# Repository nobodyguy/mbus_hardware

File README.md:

# M-bus to USB board
* KiCAD 6.X required 
* includes ESD (USB+MBUS) and TVS (MBUS) protections
* includes AP3015 stepup from 5V -> 34V
* includes CH340E UART IC

## Software
Tested with https://github.com/ganehag/pyMeterBus library.

## 5V vs 3.3V note 
CH340E is 5V only IC without additional 3.3V regulator. Even its RX/TX pins are 5V.
Use PL2303GL instead when CH340E is not available and change MBUS logic to 3.3V (replace R6 and R10).

## Board overview

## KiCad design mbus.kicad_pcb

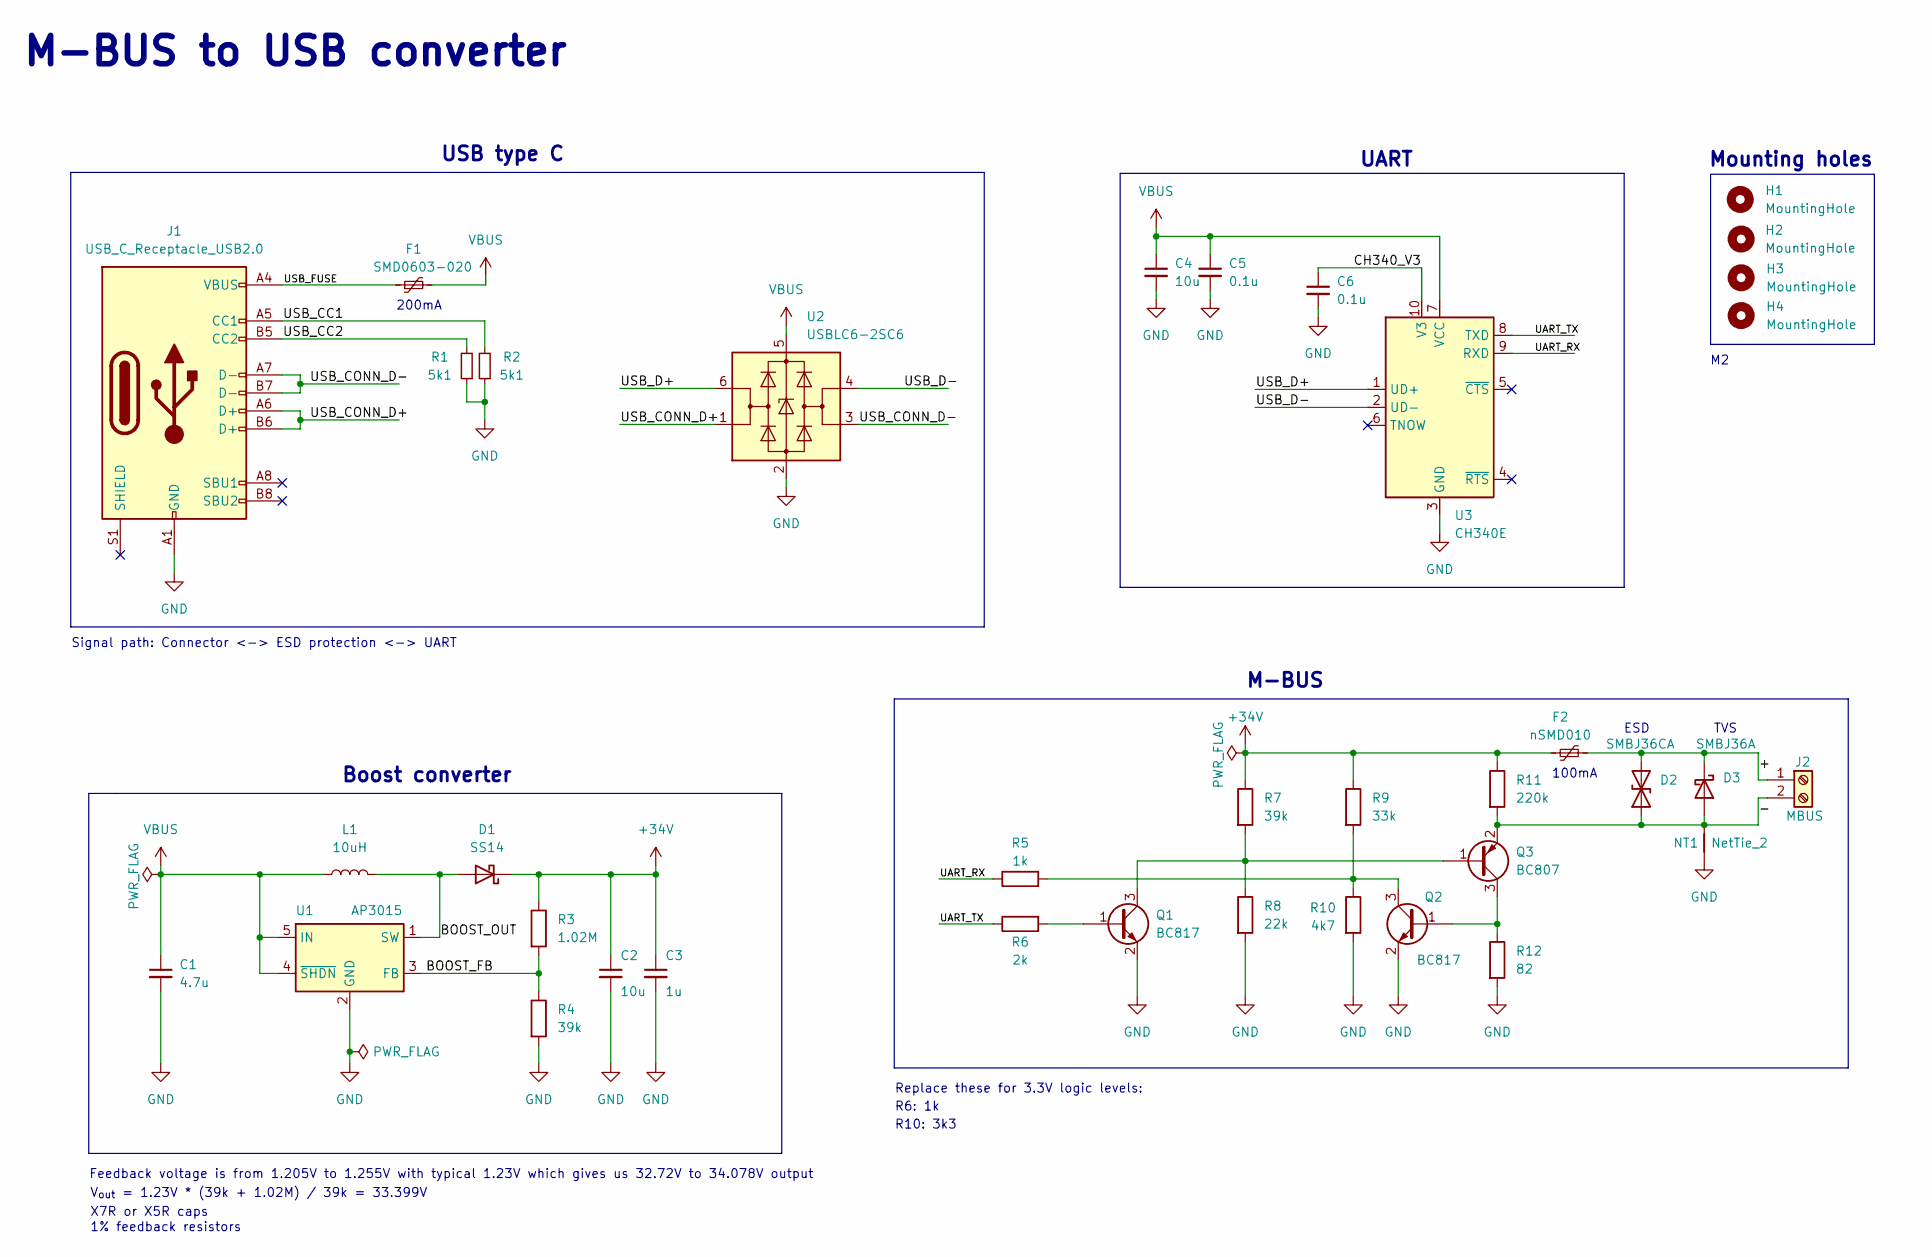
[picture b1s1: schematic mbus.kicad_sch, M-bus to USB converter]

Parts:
C1: 4.7u; C_0603_1608Metric; LCSC Part C1705
C2: 10u; C_0603_1608Metric; LCSC Part C2911377
C3: 1u; C_0603_1608Metric; LCSC Part C77386
C4: 10u; C_0603_1608Metric; LCSC Part C109455
C5, C6: 0.1u; C_0603_1608Metric; LCSC Part C14663
D1: SS14; D_SOD-123F; LCSC Part C190475
D2: SMBJ36CA; D_SMB; LCSC Part C83326
D3: SMBJ36A; D_SMB; LCSC Part C84731
F1: SMD0603-020; Fuse_0603_1608Metric; LCSC Part C2760255
F2: nSMD010; Fuse_1206_3216Metric; LCSC Part C70065
H1, H2, H3, H4: MountingHole; MountingHole_2.2mm_M2
J1: USB_C_Receptacle_USB2.0; USB_C_Receptacle_HRO_TYPE-C-31-M-12; LCSC Part C165948
J2: MBUS; TerminalBlock_Phoenix_PT-1,5-2-5.0-H_1x02_P5.00mm_Horizontal; LCSC Part C474881
L1: 10uH; L_Sunlord_MWSA0518_5.4x5.2mm; LCSC Part C408412
NT1: NetTie_2; NetTie-2_SMD_Pad0.5mm
Q1, Q2: BC817; SOT-23; LCSC Part C604682
Q3: BC807; SOT-23; LCSC Part C82369
R1, R2: 5k1; R_0603_1608Metric; LCSC Part C105580
R3: 1.02M; R_0603_1608Metric; LCSC Part C227665
R4, R7: 39k; R_0603_1608Metric; LCSC Part C118370
R5: 1k; R_0603_1608Metric; LCSC Part C966204
R6: 2k; R_0603_1608Metric; LCSC Part C445827
R8: 22k; R_0603_1608Metric; LCSC Part C441928
R9: 33k; R_0603_1608Metric; LCSC Part C441899
R10: 4k7; R_0603_1608Metric; LCSC Part C441894
R11: 220k; R_0603_1608Metric; LCSC Part C441934
R12: 82; R_0603_1608Metric; LCSC Part C445805
U1: AP3015; SOT-23-5; LCSC Part C151334
U2: USBLC6-2SC6; SOT-23-6; LCSC Part C2827654
U3: CH340E; MSOP-10_3x3mm_P0.5mm; LCSC Part C99652

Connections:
+34V: C2.1, C3.1, D1.1 (K), F2.1, R3.1, R7.1, R9.1, R11.1
/+: D2.2 (A2), D3.1 (K), F2.2, J2.1
/-: D2.1 (A1), D3.2 (A), J2.2, NT1.2, Q3.2 (E), R11.2
/BOOST_FB: R3.2, R4.1, U1.3 (FB)
/BOOST_OUT: D1.2 (A), L1.2, U1.1 (SW)
/CH340_V3: C6.1, U3.10 (V3)
/UART_RX: R5.1, U3.9 (RXD)
/UART_TX: R6.1, U3.8 (TXD)
/USB_CC1: J1.A5 (CC1), R2.2
/USB_CC2: J1.B5 (CC2), R1.2
/USB_CONN_D+: J1.A6 (D+), J1.B6 (D+), U2.1 (I/O1)
/USB_CONN_D-: J1.A7 (D-), J1.B7 (D-), U2.3 (I/O2)
/USB_D+: U2.6 (I/O1), U3.1 (UD+)
/USB_D-: U2.4 (I/O2), U3.2 (UD-)
/USB_FUSE: F1.1, J1.A4 (VBUS), J1.A9 (VBUS), J1.B4 (VBUS), J1.B9 (VBUS)
GND: C1.2, C2.2, C3.2, C4.2, C5.2, C6.2, J1.A1 (GND), J1.A12 (GND), J1.B1 (GND), J1.B12 (GND), NT1.1, Q1.2 (E), Q2.2 (E), R1.1, R2.1, R4.2, R8.2, R10.2, R12.2, U1.2 (GND), U2.2 (GND), U3.3 (GND)
unnamed: Q1.1 (B), R6.2
unnamed: Q1.3 (C), Q3.1 (B), R7.2, R8.1
unnamed: Q2.1 (B), Q3.3 (C), R12.1
unnamed: Q2.3 (C), R5.2, R9.2, R10.1
VBUS: C1.1, C4.1, C5.1, F1.2, L1.1, U1.4 (~SHDN), U1.5 (IN), U2.5 (VBUS), U3.7 (VCC)

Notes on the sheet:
R10: 3k3
V_{out} = 1.23V * (39k + 1.02M) / 39k = 33.399V
UART
Boost converter
100mA
TVS
Replace these for 3.3V logic levels:
USB type C
200mA
ESD
M-BUS
Mounting holes
Signal path: Connector <-> ESD protection <-> UART
X7R or X5R caps
Feedback voltage is from 1.205V to 1.255V with typical 1.23V which gives us 32.72V to 34.078V output
R6: 1k
M-BUS to USB converter
1% feedback resistors

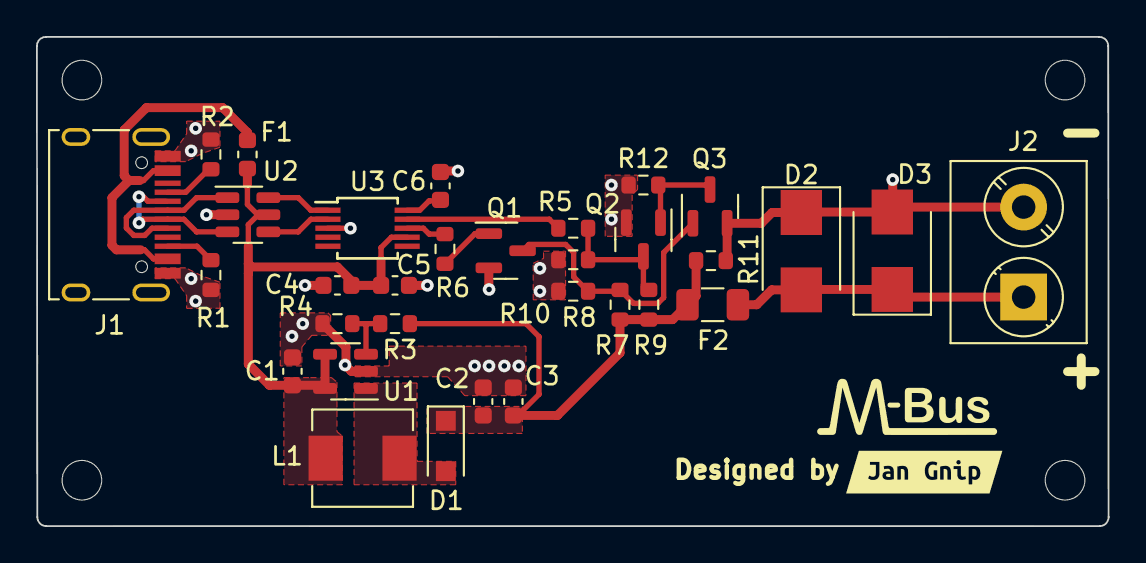
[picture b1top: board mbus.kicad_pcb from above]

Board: 2 copper layers, 59.5 x 27.2 mm, 38 parts (0 on the bottom side), 21 nets.

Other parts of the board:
kibuzzard-62A19C5B: G***; kibuzzard-62A19C5B

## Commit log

2022-03-18 Finished USB
2022-03-18 Replaced readme
2022-03-18 Removed obsolete project file
2022-03-19 mbus driving logic WIP
2022-03-21 Added boost converter, protection components for mbus
2022-03-23 Generated designators
2022-04-05 Replaced 500mA VBUS fuse with 200mA, changed MBUS circuit to work with 5V logic
2022-04-05 Added 5V/3.3V note to readme
2022-04-05 Replaced CH340N by CH340E
2022-04-05 Added microUSB footprint with 3D model
2022-04-07 Added part numbers, schematic to readme and symbol for mbus power rail
2022-04-10 Replaced microUSB with type C, changed ESD protection IC
2022-04-10 Fixed footprint library link, updated exported schematic
2022-04-16 PCB component placement WIP
2022-04-18 PCB placement done
2022-04-18 Added mounting holes, board outline done
2022-04-19 PCB rev0.1 finished
2022-04-19 Added manufacturing exports
2022-04-19 Fixed LCSC part IDs
2022-04-20 Added CH340N symbol just in case, added part numbers for the rest of the passive components
2022-04-26 Added final PCB image and 3D render
2022-04-26 Updated manufacturing exports
2022-04-26 Fixed USB connector shield pins net to pass DRC
2022-06-09 rev 0.2 - swapped RX/TX pins
2022-06-28 Added photo of working board
2022-06-28 Tested software note
2022-07-04 Added 3D box model
2022-07-04 Exported 3D box
2022-09-17 Added iBOM
2022-09-17 Changes to enclosure, added TVS nettie
